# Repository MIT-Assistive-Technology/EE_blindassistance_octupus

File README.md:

# EE_blindassistance_octupus
Electrical Engineering/Hardware Side of Blind Assistance! [Team Octupus!]

## What is here

| Folder | What |
|---|---|
| `PCB_Wristband/` | KiCad project for the haptic wristband |
| `lamb_v2/` | **Lamb (v2)**, the IMU logging / dead-reckoning test app (branch `imu-test-code`). Do not edit from the Octopi work; it is our test setup. |
| `Package.swift`, `Octopi/Sources/OctopiCore` | **OctopiCore**, the product app's logic as a Swift package. It compiles the step/heading pipeline from `lamb_v2/Path Construction` unmodified, plus anchors, paths, RSSI, left-behind detection, navigation, haptics and the session coordinator. |
| `Octopi/Tests/OctopiCoreTests` | Unit tests for the core (Swift Testing) |
| `Octopi/App`, `Octopi/Octopi.xcodeproj` | **Octopi**, the accessible iOS app (SwiftUI) |
| `Octopi/UITests` | XCUITest that runs Apple's accessibility audit on every screen |
| `scripts/a11y_lint.py` | Static accessibility lint for the SwiftUI sources |

## Build and test

Core logic tests (macOS, no simulator needed):

```bash
swift test
```

Open the app in Xcode: `Octopi/Octopi.xcodeproj`, scheme `Octopi`. Or from the command line:

```bash
xcodebuild -project Octopi/Octopi.xcodeproj -scheme Octopi -destination 'platform=iOS Simulator,name=iPhone 17,OS=26.2' build
```

Design notes (plan, accessibility rules, hardware interface contract, pack format, screenshots) live in a local
`docs/` folder that is not committed.

Accessibility checks:

```bash
python3 scripts/a11y_lint.py Octopi/App
```

```bash
xcodebuild -project Octopi/Octopi.xcodeproj -scheme Octopi -destination 'platform=iOS Simulator,name=iPhone 17,OS=26.2' -only-testing:OctopiUITests test
```

In the iOS simulator the app runs with a **hardware simulator** (band, beacons, walking, GPS) so
the whole flow can be tried without hardware: Settings → Simulator controls. On a real phone the
simulator is off unless launched with `-simulateHardware`.

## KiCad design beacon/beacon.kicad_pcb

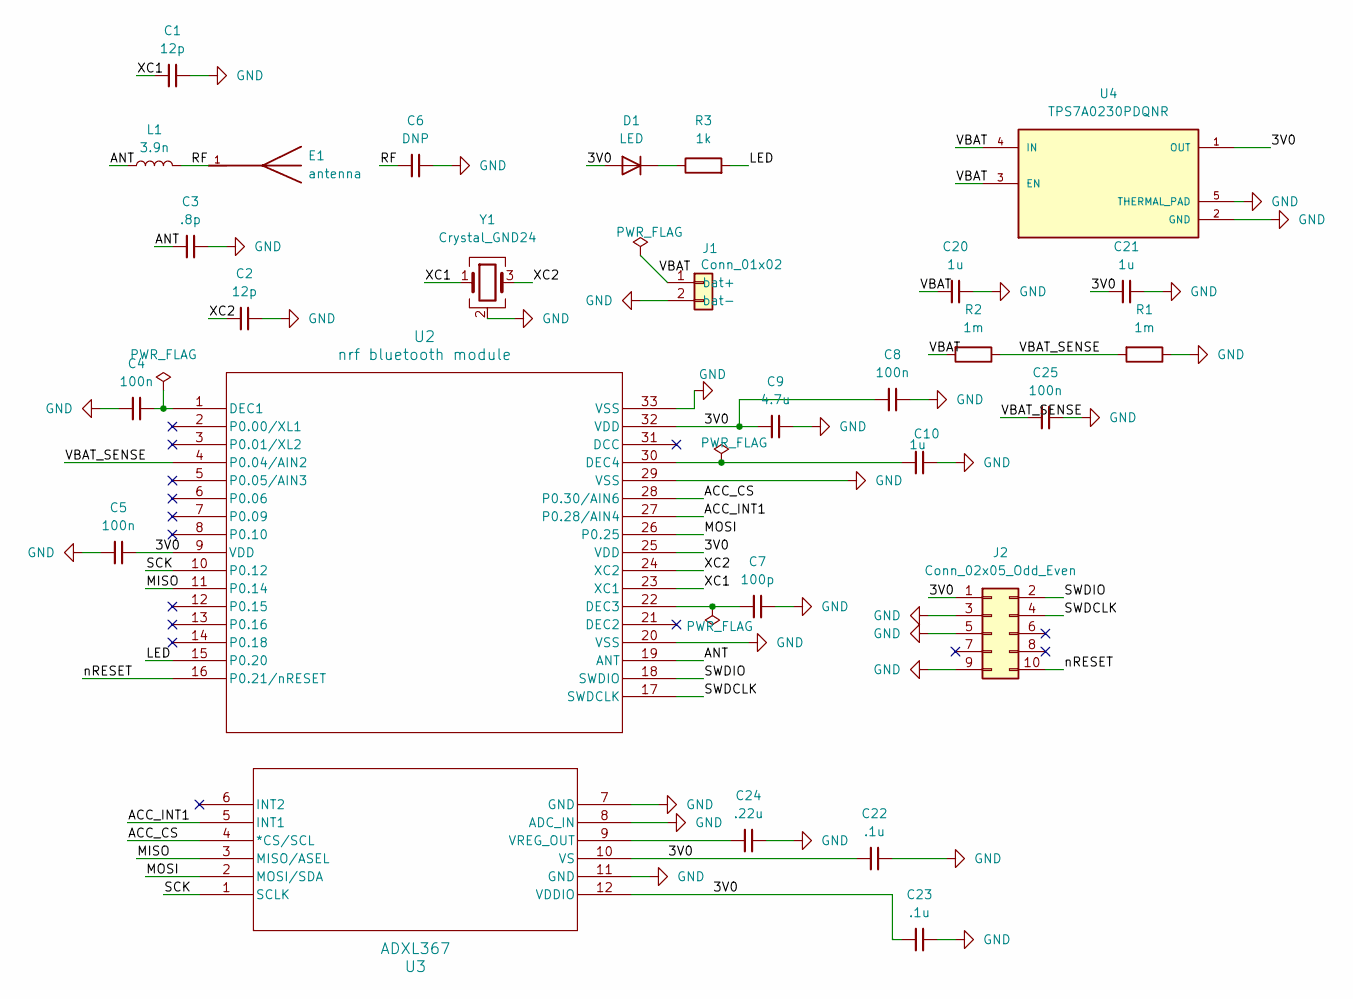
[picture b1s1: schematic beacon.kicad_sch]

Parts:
C1, C2: 12p; C_0402_1005Metric
C3: .8p; C_0402_1005Metric
C4, C5, C8, C25: 100n; C_0402_1005Metric
C6: DNP; C_0402_1005Metric
C7: 100p; C_0402_1005Metric
C9: 4.7u; C_0603_1608Metric
C10: 1u; C_0603_1608Metric
C20, C21: 1u; C_0402_1005Metric
C22, C23: .1u; C_0402_1005Metric
C24: .22u; C_0402_1005Metric
D1: LED; LED_0603_1608Metric
E1: antenna; XCVR_2450AT18A0100001E; PARTREV 4.0; DigiKey_Part_Number 712-2450AT18A0100001ECT-ND
J1: Conn_01x02; JST_PH_S2B-PH-SM4-TB_1x02-1MP_P2.00mm_Horizontal
J2: Conn_02x05_Odd_Even; PinHeader_2x05_P1.27mm_Vertical_SMD
L1: 3.9n; L_0402_1005Metric
R1, R2: 1m; R_0402_1005Metric
R3: 1k; R_0402_1005Metric
U2: nrf bluetooth module; QFN-32-1EP_5x5mm_P0.5mm_EP3.6x3.6mm
U3: ADXL367; LGA-12_2x2mm_P0.5mm
U4: TPS7A0230PDQNR; IC_TPS7A0230PDQNR; PARTREV C
Y1: Crystal_GND24; Crystal_SMD_2016-4Pin_2.0x1.6mm

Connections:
/3V0: C5.2, C8.1, C9.1, C21.1, C22.1, C23.1, D1.2 (A), J2.1, U2.9 (VDD), U2.25 (VDD), U2.32 (VDD), U3.10 (VS), U3.12 (VDDIO), U4.1 (OUT)
/ACC_CS: U2.28 (P0.30/AIN6), U3.4 (*CS/SCL)
/ACC_INT1: U2.27 (P0.28/AIN4), U3.5 (INT1)
/ANT: C3.1, L1.1, U2.19 (ANT)
/LED: R3.2, U2.15 (P0.20)
/MISO: U2.11 (P0.14), U3.3 (MISO/ASEL)
/MOSI: U2.26 (P0.25), U3.2 (MOSI/SDA)
/RF: C6.1, E1.1, L1.2
/SCK: U2.10 (P0.12), U3.1 (SCLK)
/SWDCLK: J2.4, U2.17 (SWDCLK)
/SWDIO: J2.2, U2.18 (SWDIO)
/VBAT: C20.1, J1.1 (bat+), R2.2, U4.3 (EN), U4.4 (IN)
/VBAT_SENSE: C25.1, R1.2, R2.1, U2.4 (P0.04/AIN2)
/XC1: C1.2, U2.23 (XC1), Y1.1
/XC2: C2.1, U2.24 (XC2), Y1.3
/nRESET: J2.10, U2.16 (P0.21/nRESET)
GND: C1.1, C2.2, C3.2, C4.1, C5.1, C6.2, C7.2, C8.2, C9.2, C10.2, C20.2, C21.2, C22.2, C23.2, C24.2, C25.2, J1.2 (bat-), J2.3, J2.5, J2.9, R1.1, U2.20 (VSS), U2.29 (VSS), U2.33 (VSS), U3.7 (GND), U3.8 (ADC_IN), U3.11 (GND), U4.2 (GND), U4.5 (THERMAL_PAD), Y1.2 (G), Y1.4 (G)
unnamed: D1.1 (K), R3.1
unnamed: C4.2, U2.1 (DEC1)
unnamed: C7.1, U2.22 (DEC3)
unnamed: C10.1, U2.30 (DEC4)
unnamed: C24.1, U3.9 (VREG_OUT)

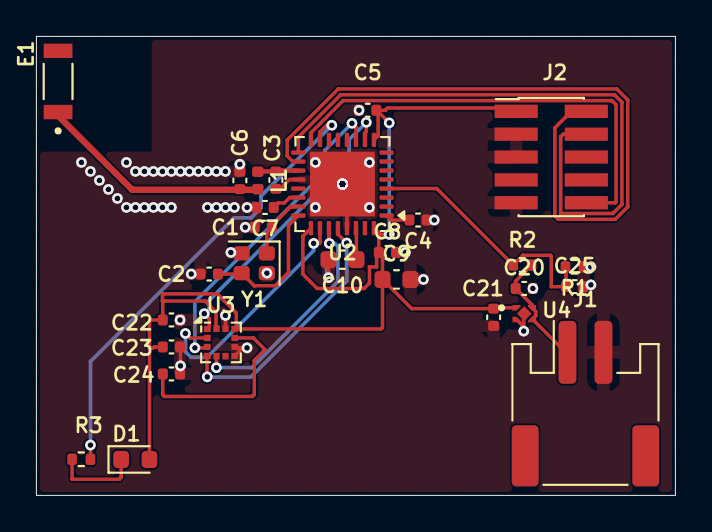
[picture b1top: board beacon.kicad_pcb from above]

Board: 4 copper layers, 35.5 x 25.5 mm, 28 parts (0 on the bottom side), 22 nets.

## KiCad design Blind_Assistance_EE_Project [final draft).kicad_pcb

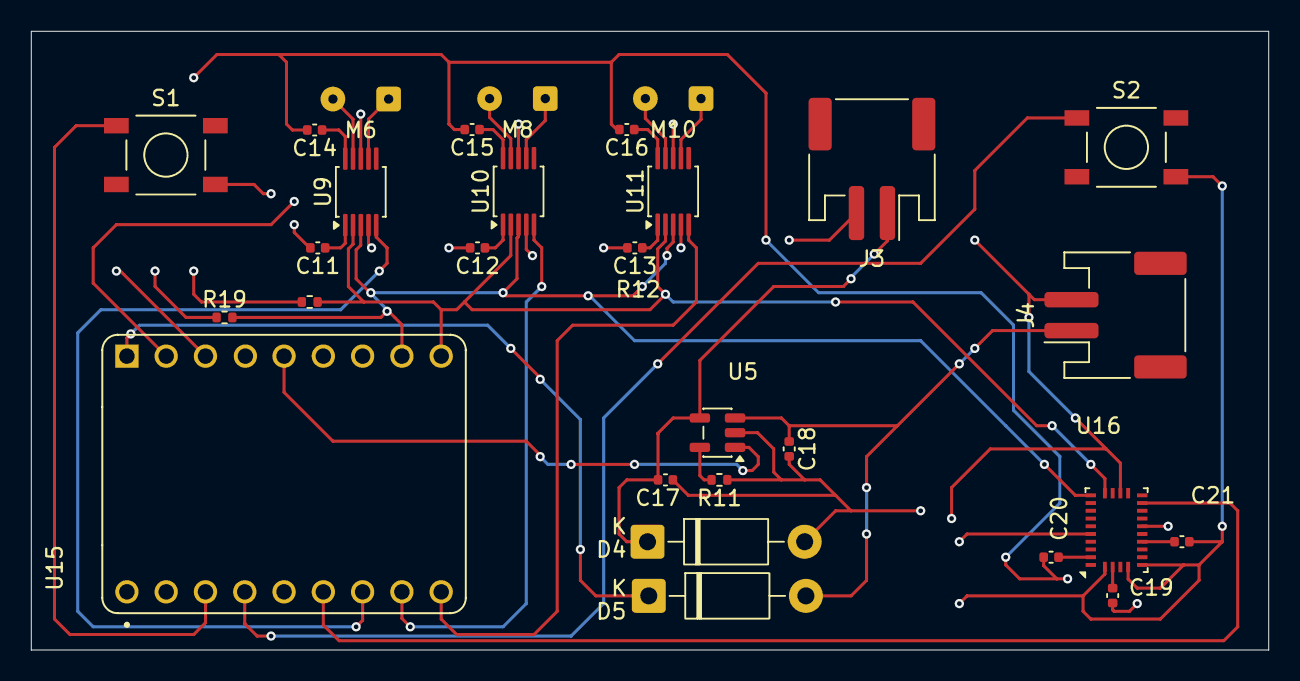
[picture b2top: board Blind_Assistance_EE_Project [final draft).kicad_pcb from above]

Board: 2 copper layers, 80.0 x 40.0 mm, 29 parts (0 on the bottom side), 30 nets.

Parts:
C11, C12, C13, C14, C15, C16: 1uF; C_0402_1005Metric
C17, C18: 4.7uF; C_0402_1005Metric
C19, C20, C21: 100nF; C_0402_1005Metric
D4: D_TVS; D_DO-41_SOD81_P10.16mm_Horizontal
D5: 1N5819; D_DO-41_SOD81_P10.16mm_Horizontal
J3: Qi receiver 1407; JST_PH_S2B-PH-SM4-TB_1x02-1MP_P2.00mm_Horizontal
J4: Adafruit 1578; JST_PH_S2B-PH-SM4-TB_1x02-1MP_P2.00mm_Horizontal
M6, M8, M10: Motor_AC; SolderWire-0.1sqmm_1x02_P3.6mm_D0.4mm_OD1mm
R11: 5kohm; R_0402_1005Metric
R12, R19: 4.7Kohm; R_0402_1005Metric
S1, S2: PTS525SM15SMTR2LFS; SW_PTS525SM15SMTR2LFS
U5: MCP73831-2-OT; SOT-23-5
U9, U10, U11: DRV2605LDGS; TSSOP-10_3x3mm_P0.5mm
U15: ESP32-S3-SuperMini; ESP32-S3-SuperMini (1)
U16: BNO055; LGA-28_5.2x3.8mm_P0.5mm

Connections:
+3V3: C14.2, C15.2, C16.2, C19.1, C20.2, R12.1, R19.1, U15.3V3, U16.11 (~RESET)
GND: C11.2, C12.2, C13.2, C17.1, C18.2, C21.1, D4.2 (A2), J3.2, J4.2, R11.1, S1.4, S2.4, U5.2 (V_{SS}), U9.4 (IN/TRIG), U9.8 (GND), U10.4 (IN/TRIG), U10.8 (GND), U11.4 (IN/TRIG), U11.8 (GND), U15.GND, U16.2 (GND), U16.5 (PS1), U16.6 (PS0), U16.17 (COM3), U16.25 (GNDIO)
unnamed: C17.2, D4.1 (A1), J3.1, U5.4 (V_{DD})
unnamed: C18.1, D5.2 (A), J4.1, U5.3 (V_{BAT})
unnamed: D5.1 (K), U15.5V
unnamed: R11.2, U5.5 (PROG)
unnamed: M6.1, U9.7 (OUT+)
unnamed: M6.2, U9.9 (OUT-)
unnamed: C11.1, U9.1 (REG)
unnamed: C14.1, U9.10 (VDD)
unnamed: U10.5 (EN), U15.6 (GPIO_6)
unnamed: M8.1, U10.7 (OUT+)
unnamed: M8.2, U10.9 (OUT-)
unnamed: C12.1, U10.1 (REG)
unnamed: R12.2, U9.2 (SCL), U10.2 (SCL), U11.2 (SCL), U15.8 (GPIO_8), U16.19 (COM1)
unnamed: R19.2, U9.3 (SDA), U10.3 (SDA), U11.3 (SDA), U15.9 (GPIO_9), U16.20 (COM0)
unnamed: C15.1, U10.10 (VDD)
unnamed: U11.5 (EN), U15.7 (GPIO_7)
unnamed: M10.1, U11.7 (OUT+)
unnamed: M10.2, U11.9 (OUT-)
unnamed: C13.1, U11.1 (REG)
unnamed: C16.1, U11.10 (VDD)
unnamed: S1.1, U15.1 (GPIO_1)
unnamed: S2.1, U15.2 (GPIO_2)
unnamed: U15.4 (GPIO_4), U16.14 (INT)
unnamed: U9.5 (EN), U15.5 (GPIO_5)
unnamed: U5.1 (STAT), U15.12 (GPIO_12)
unnamed: C21.2, U16.9 (CAP)
unnamed: C19.2, U16.3 (VDD)
unnamed: C20.1, U16.28 (VDDIO)
